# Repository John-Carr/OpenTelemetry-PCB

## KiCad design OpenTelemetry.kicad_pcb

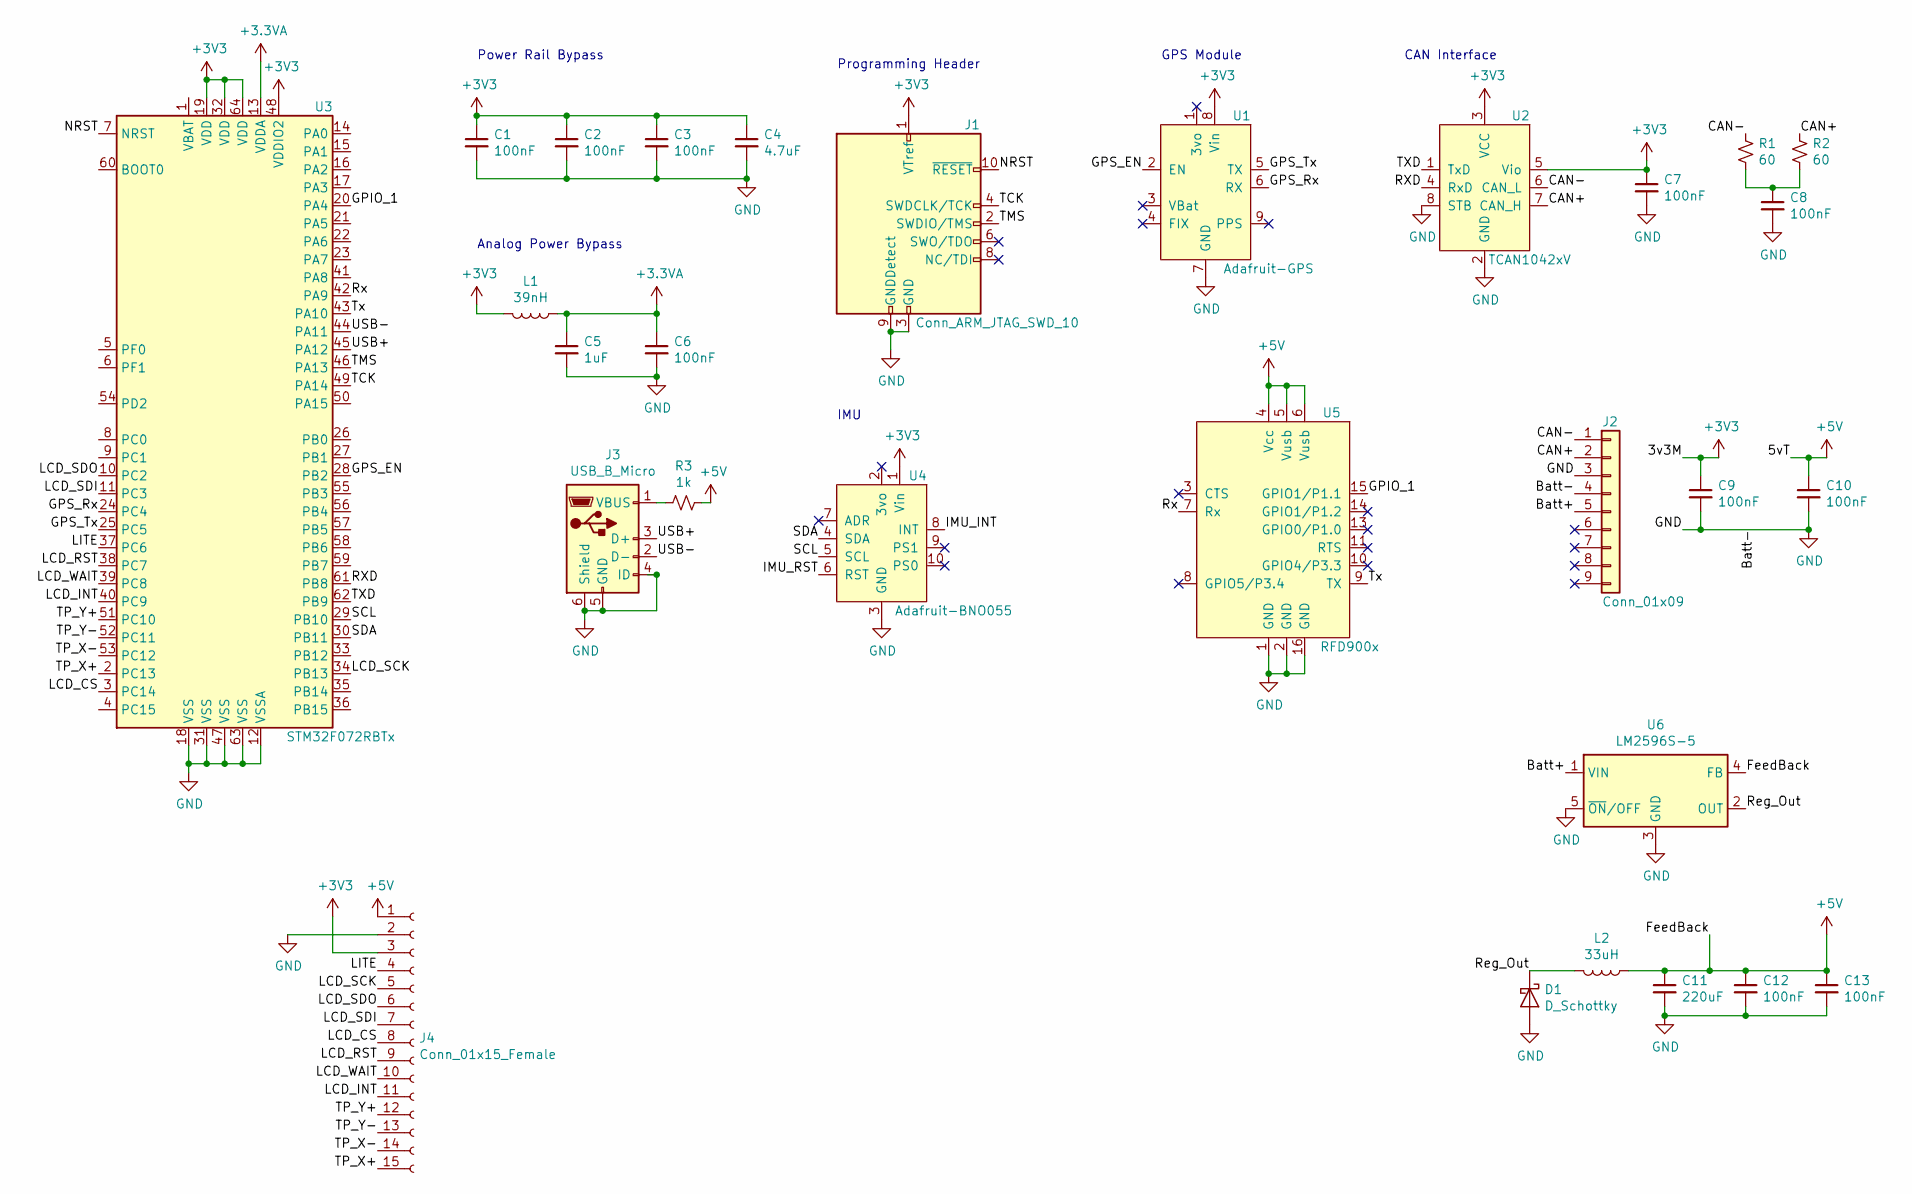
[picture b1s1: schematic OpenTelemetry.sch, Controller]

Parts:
C1, C2, C3, C6, C7, C8, C9, C10, C12, C13: 100nF; C_0603_1608Metric
C4: 4.7uF; C_0805_2012Metric
C5: 1uF; C_0603_1608Metric
C11: 220uF; CP_Elec_8x10; LCSC C134520
D1: D_Schottky; D_SMA; LCSC C22452
J1: Conn_ARM_JTAG_SWD_10; PinHeader_2x05_P1.27mm_Vertical
J2: Conn_01x09; Molex_Micro-Fit_3.0_43650-0915_1x09_P3.00mm_Vertical
J3: USB_B_Micro; USB_Micro-B_Molex_47346-0001
J4: Conn_01x15_Female; PinHeader_1x15_P2.54mm_Vertical
L1: 39nH; L_0402_1005Metric
L2: 33uH; L_TDK_SLF7045; LCSC C39340
R1, R2: 60; R_0603_1608Metric
R3: 1k; R_0805_2012Metric
U1: Adafruit-GPS
U2: TCAN1042xV; SOIC-8
U3: STM32F072RBTx; LQFP-64_10x10mm_P0.5mm
U4: Adafruit-BNO055
U5: RFD900x
U6: LM2596S-5; TO-263-5_TabPin3; LCSC C10002

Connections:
+3.3VA: C5.1, C6.1, L1.1, U3.13 (VDDA)
+3V3: C1.1, C2.1, C3.1, C4.1, C7.1, C9.1, J1.1 (VTref), J4.3, L1.2, U1.8 (Vin), U2.3 (VCC), U2.5 (Vio), U3.19 (VDD), U3.32 (VDD), U3.48 (VDDIO2), U3.64 (VDD), U4.1 (Vin)
+5V: C10.1, C11.1, C12.1, C13.1, J4.1, L2.1, R3.1, U5.4 (Vcc), U5.5 (Vusb), U5.6 (Vusb), U6.4 (FB)
/Batt+: J2.5, U6.1 (VIN)
/CAN+: J2.2, R2.1, U2.7 (CAN_H)
/CAN-: J2.1, R1.1, U2.6 (CAN_L)
/GPIO_1: U3.20 (PA4), U5.15 (GPIO1/P1.1)
/GPS_EN: U1.2 (EN), U3.28 (PB2)
/GPS_Rx: U1.6 (RX), U3.24 (PC4)
/GPS_Tx: U1.5 (TX), U3.25 (PC5)
/IMU_INT: U4.8 (INT)
/IMU_RST: U4.6 (RST)
/LCD_CS: J4.8, U3.3 (PC14)
/LCD_INT: J4.11, U3.40 (PC9)
/LCD_RST: J4.9, U3.38 (PC7)
/LCD_SCK: J4.5, U3.34 (PB13)
/LCD_SDI: J4.7, U3.11 (PC3)
/LCD_SDO: J4.6, U3.10 (PC2)
/LCD_WAIT: J4.10, U3.39 (PC8)
/LITE: J4.4, U3.37 (PC6)
/NRST: J1.10 (~RESET~), U3.7 (NRST)
/RXD: U2.4 (RxD), U3.61 (PB8)
/Reg_Out: D1.1 (K), L2.2, U6.2 (OUT)
/Rx: U3.42 (PA9), U5.7 (Rx)
/SCL: U3.29 (PB10), U4.5 (SCL)
/SDA: U3.30 (PB11), U4.4 (SDA)
/TCK: J1.4 (SWDCLK/TCK), U3.49 (PA14)
/TMS: J1.2 (SWDIO/TMS), U3.46 (PA13)
/TP_X+: J4.15, U3.2 (PC13)
/TP_X-: J4.14, U3.53 (PC12)
/TP_Y+: J4.12, U3.51 (PC10)
/TP_Y-: J4.13, U3.52 (PC11)
/TXD: U2.1 (TxD), U3.62 (PB9)
/Tx: U3.43 (PA10), U5.9 (TX)
/USB+: J3.3 (D+), U3.45 (PA12)
/USB-: J3.2 (D-), U3.44 (PA11)
GND: C1.2, C2.2, C3.2, C4.2, C5.2, C6.2, C7.2, C8.2, C9.2, C10.2, C11.2, C12.2, C13.2, D1.2 (A), J1.3 (GND), J1.5 (GND), J1.9 (GNDDetect), J2.3, J2.4, J3.4 (ID), J3.5 (GND), J3.6 (Shield), J4.2, U1.7 (GND), U2.2 (GND), U2.8 (STB), U3.12 (VSSA), U3.18 (VSS), U3.31 (VSS), U3.47 (VSS), U3.63 (VSS), U4.3 (GND), U5.1 (GND), U5.2 (GND), U5.16 (GND), U6.3 (GND), U6.5 (~ON~/OFF)
unnamed: C8.1, R1.2, R2.2
unnamed: J3.1 (VBUS), R3.2

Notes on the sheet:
Power Rail Bypass
Analog Power Bypass
Programming Header
CAN Interface
GPS Module
IMU

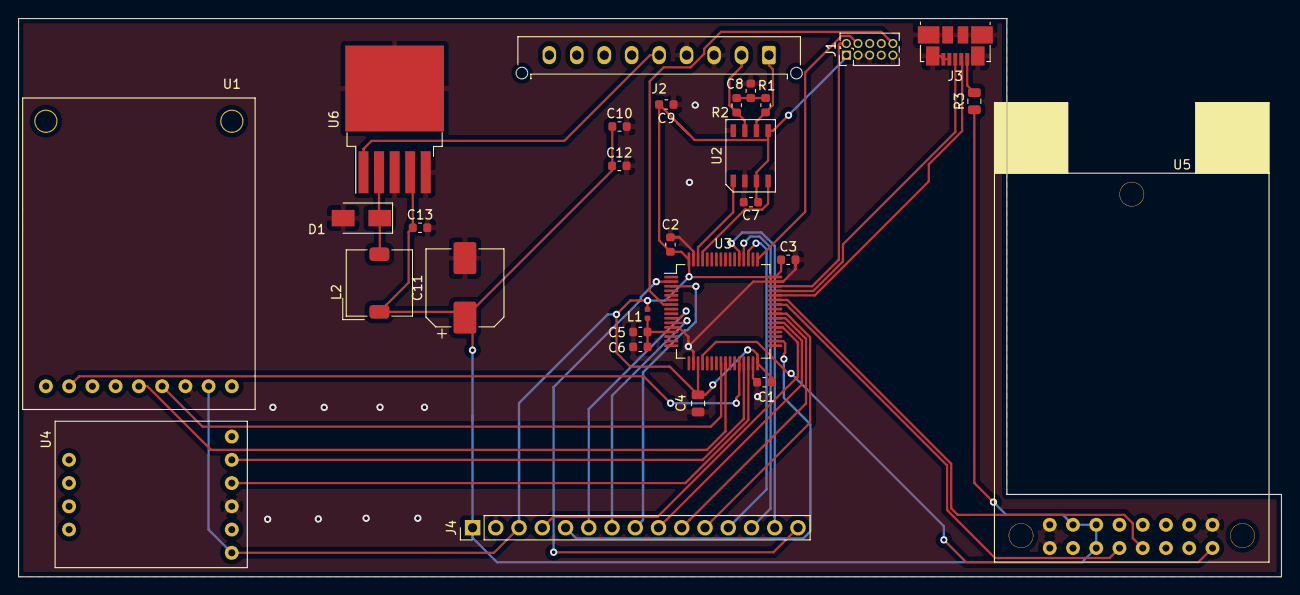
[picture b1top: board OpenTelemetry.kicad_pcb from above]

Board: 2 copper layers, 138.0 x 61.0 mm, 29 parts (0 on the bottom side), 37 nets.

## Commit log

2021-03-22 Added git ignore
2021-03-22 Initial PCB
2021-05-06 V1 finished
